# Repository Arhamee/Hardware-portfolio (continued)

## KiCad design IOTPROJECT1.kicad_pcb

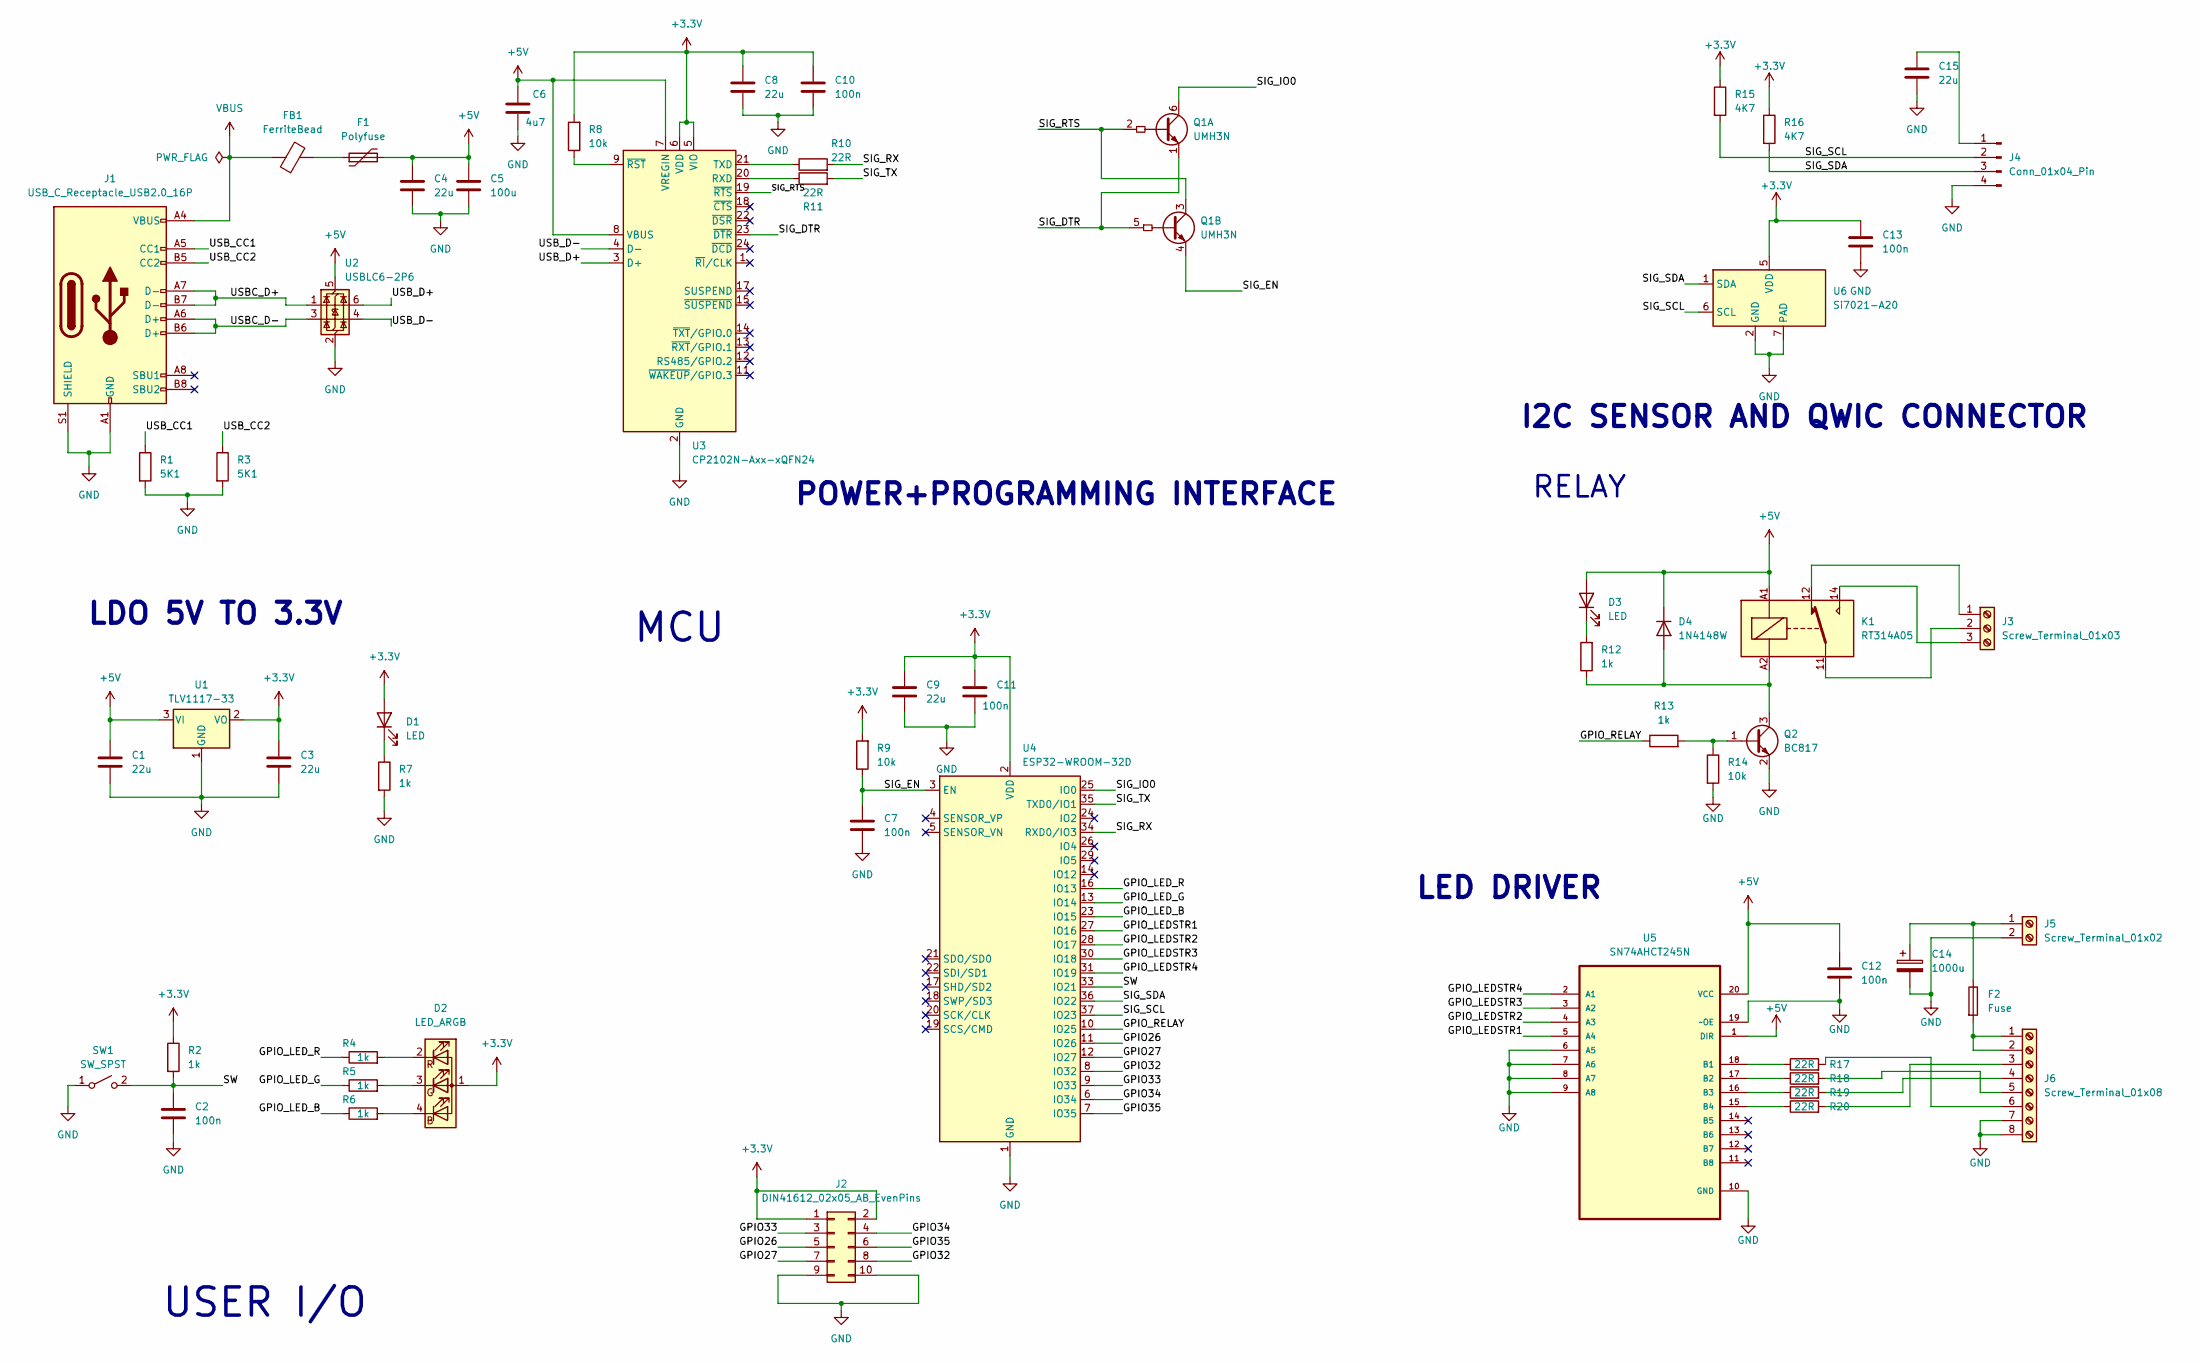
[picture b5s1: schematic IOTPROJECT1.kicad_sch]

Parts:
C1, C3, C4, C8, C9, C15: 22u; C_0805_2012Metric_Pad1.18x1.45mm_HandSolder
C2, C7, C10, C11, C12, C13: 100n; C_0402_1005Metric_Pad0.74x0.62mm_HandSolder
C5: 100u; C_0402_1005Metric_Pad0.74x0.62mm_HandSolder
C6: 4u7; C_0805_2012Metric_Pad1.18x1.45mm_HandSolder
C14: 1000u; CP_Radial_D10.0mm_P5.00mm
D1, D3: LED; LED_0402_1005Metric_Pad0.77x0.64mm_HandSolder
D2: LED_ARGB; LED_Cree-PLCC4_3.2x2.8mm_CCW
D4: 1N4148W; D_SOD-123
F1: Polyfuse; Fuse_1206_3216Metric_Pad1.42x1.75mm_HandSolder
F2: Fuse; FUSE_696105003002
FB1: FerriteBead; L_0603_1608Metric_Pad1.05x0.95mm_HandSolder
J1: USB_C_Receptacle_USB2.0_16P; USB_C_Receptacle_GCT_USB4105-xx-A_16P_TopMnt_Horizontal
J2: DIN41612_02x05_AB_EvenPins; PinHeader_2x05_P2.54mm_Vertical
J3: Screw_Terminal_01x03; TerminalBlock_Phoenix_MKDS-1,5-3_1x03_P5.00mm_Horizontal
J4: Conn_01x04_Pin; Molex_PicoBlade_53048-0410_1x04_P1.25mm_Horizontal
J5: Screw_Terminal_01x02; TerminalBlock_Phoenix_MKDS-1,5-2-5.08_1x02_P5.08mm_Horizont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
J6: Screw_Terminal_01x08; TerminalBlock_Phoenix_MKDS-1,5-8-5.08_1x08_P5.08mm_Horizont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
K1: RT314A05; Relay_SPDT_Schrack-RT1-16A-FormC_RM5mm
Q1: UMH3N; SOT-363_SC-70-6
Q2: BC817; SOT-23
R1, R3: 5K1; R_0402_1005Metric_Pad0.72x0.64mm_HandSolder
R2, R4, R5, R6, R7, R12, R13: 1k; R_0402_1005Metric_Pad0.72x0.64mm_HandSolder
R8, R9, R14: 10k; R_0402_1005Metric_Pad0.72x0.64mm_HandSolder
R10, R11, R17, R18, R19, R20: 22R; R_0402_1005Metric_Pad0.72x0.64mm_HandSolder
R15, R16: 4K7; R_0402_1005Metric_Pad0.72x0.64mm_HandSolder
SW1: SW_SPST; SW_SPST_CK_RS282G05A3
U1: TLV1117-33; SOT-223-3_TabPin2
U2: USBLC6-2P6; SOT-666
U3: CP2102N-Axx-xQFN24; QFN-24-1EP_4x4mm_P0.5mm_EP2.6x2.6mm
U4: ESP32-WROOM-32D
U5: SN74AHCT245N; DIP254P762X508-20; MPN SN74AHCT245N
U6: Si7021-A20; DFN-6-1EP_3x3mm_P1mm_EP1.5x2.4mm

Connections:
+3.3V: C3.1, C8.1, C9.1, C10.1, C11.1, C13.1, D1.2 (A), D2.1 (A), J2.1, J2.2, R2.1, R8.2, R9.2, R15.1, R16.1, U1.2 (VO), U3.5 (VIO), U3.6 (VDD), U4.2 (VDD), U6.5 (VDD)
+5V: C1.1, C4.1, C5.1, C6.1, C12.1, D3.2 (A), D4.1 (K), F1.2, K1.A1, U1.3 (VI), U2.5 (VBUS), U3.7 (VREGIN), U3.8 (VBUS), U5.1 (DIR), U5.20 (VCC)
/GPIO26: J2.5, U4.11 (IO26)
/GPIO27: J2.7, U4.12 (IO27)
/GPIO32: J2.8, U4.8 (IO32)
/GPIO33: J2.3, U4.9 (IO33)
/GPIO34: J2.4, U4.6 (IO34)
/GPIO35: J2.6, U4.7 (IO35)
/GPIO_LEDSTR1: U4.27 (IO16), U5.5 (A4)
/GPIO_LEDSTR2: U4.28 (IO17), U5.4 (A3)
/GPIO_LEDSTR3: U4.30 (IO18), U5.3 (A2)
/GPIO_LEDSTR4: U4.31 (IO19), U5.2 (A1)
/GPIO_LED_B: R6.1, U4.23 (IO15)
/GPIO_LED_G: R5.1, U4.13 (IO14)
/GPIO_LED_R: R4.1, U4.16 (IO13)
/GPIO_RELAY: R13.1, U4.10 (IO25)
/SIG_DTR: Q1.1 (E1), Q1.5 (B2), U3.23 (~DTR)
/SIG_EN: C7.2, Q1.4 (E2), R9.1, U4.3 (EN)
/SIG_IO0: Q1.6 (C1), U4.25 (IO0)
/SIG_RTS: Q1.2 (B1), Q1.3 (C2), U3.19 (~RTS)
/SIG_RX: R10.2, U4.34 (RXD0/IO3)
/SIG_SCL: J4.2, R15.2, U4.37 (IO23), U6.6 (SCL)
/SIG_SDA: J4.3, R16.2, U4.36 (IO22), U6.1 (SDA)
/SIG_TX: R11.2, U4.35 (TXD0/IO1)
/SW: C2.1, R2.2, SW1.2 (B), U4.33 (IO21)
/USBC_D+: J1.A7 (D-), J1.B7 (D-), U2.1 (I/O1)
/USBC_D-: J1.A6 (D+), J1.B6 (D+), U2.3 (I/O2)
/USB_CC1: J1.A5 (CC1), R1.1
/USB_CC2: J1.B5 (CC2), R3.1
/USB_D+: U2.6 (I/O1), U3.3 (D+)
/USB_D-: U2.4 (I/O2), U3.4 (D-)
GND: C1.2, C2.2, C3.2, C4.2, C5.2, C6.2, C7.1, C8.2, C9.2, C10.2, C11.2, C12.2, C13.2, C14.2, C15.2, J1.A1 (GND), J1.A12 (GND), J1.B1 (GND), J1.B12 (GND), J1.S1 (SHIELD), J2.9, J2.10, J4.4, J5.2, J6.7, J6.8, Q2.2 (E), R1.2, R3.2, R7.2, R14.2, SW1.1 (A), U1.1 (GND), U2.2 (GND), U3.2 (GND), U3.25 (GND), U4.1 (GND), U4.15 (GND), U4.38 (GND), U4.39 (GND), U5.6 (A5), U5.7 (A6), U5.8 (A7), U5.9 (A8), U5.10 (GND), U5.19 (~OE), U6.2 (GND), U6.7 (PAD)
unnamed: D1.1 (K), R7.1
unnamed: D2.4 (BK), R6.2
unnamed: D2.3 (GK), R5.2
unnamed: D2.2 (RK), R4.2
unnamed: D3.1 (K), R12.2
unnamed: D4.2 (A), K1.A2, Q2.3 (C), R12.1
unnamed: F1.1, FB1.2
unnamed: J3.1, K1.12
unnamed: J3.2, K1.11
unnamed: J3.3, K1.14
unnamed: C15.1, J4.1
unnamed: C14.1, F2.1, J5.1
unnamed: F2.2, J6.1, J6.2
unnamed: J6.3, R20.2
unnamed: J6.4, R19.2
unnamed: J6.5, R18.2
unnamed: J6.6, R17.2
unnamed: Q2.1 (B), R13.2, R14.1
unnamed: R11.1, U3.20 (RXD)
unnamed: R10.1, U3.21 (TXD)
unnamed: R8.1, U3.9 (~RST)
unnamed: R17.1, U5.18 (B1)
unnamed: R18.1, U5.17 (B2)
unnamed: R19.1, U5.16 (B3)
unnamed: R20.1, U5.15 (B4)
VBUS: FB1.1, J1.A4 (VBUS), J1.A9 (VBUS), J1.B4 (VBUS), J1.B9 (VBUS)

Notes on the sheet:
USER I/O
LDO 5V TO 3.3V
MCU
I2C SENSOR AND QWIC CONNECTOR
POWER+PROGRAMMING INTERFACE
LED DRIVER
RELAY

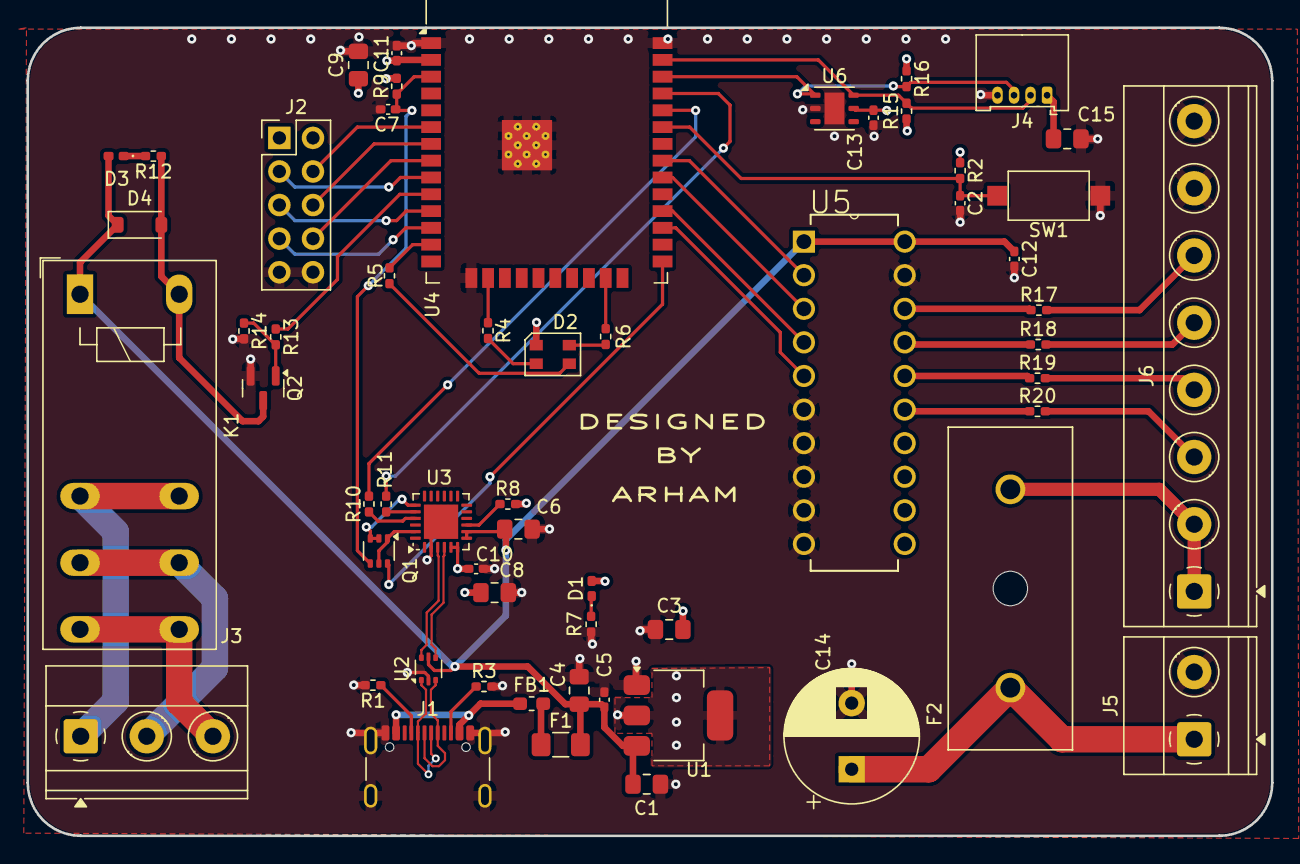
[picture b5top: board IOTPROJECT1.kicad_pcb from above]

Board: 4 copper layers, 94.1 x 61.1 mm, 58 parts (0 on the bottom side), 58 nets.
